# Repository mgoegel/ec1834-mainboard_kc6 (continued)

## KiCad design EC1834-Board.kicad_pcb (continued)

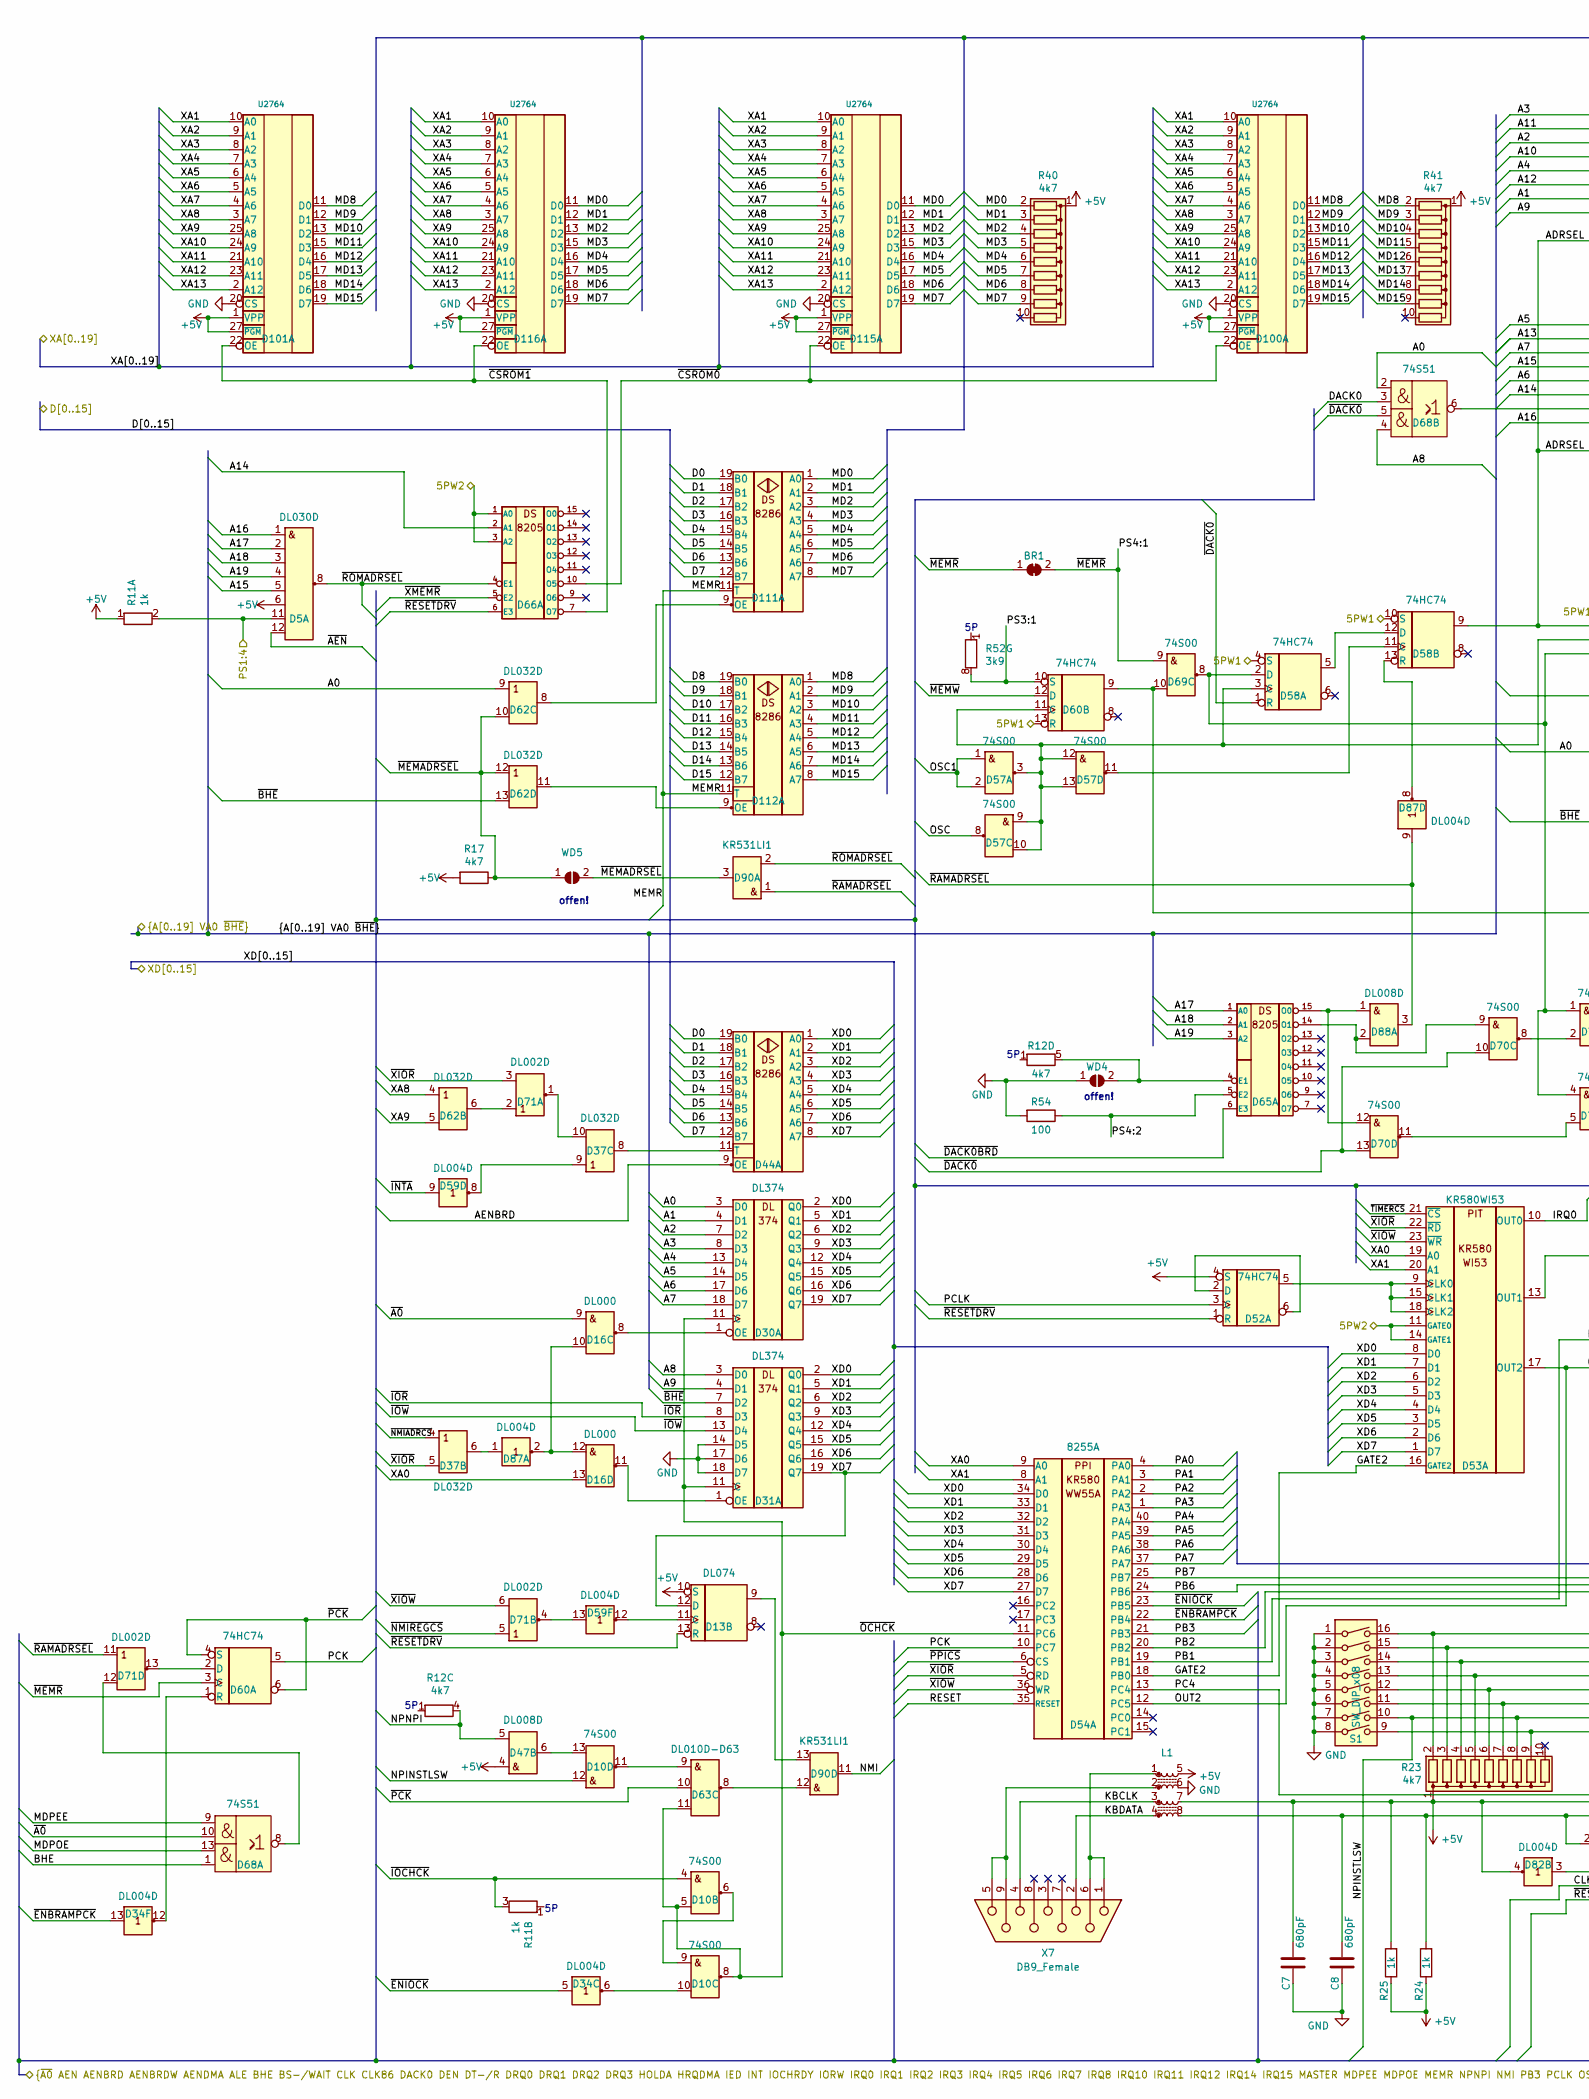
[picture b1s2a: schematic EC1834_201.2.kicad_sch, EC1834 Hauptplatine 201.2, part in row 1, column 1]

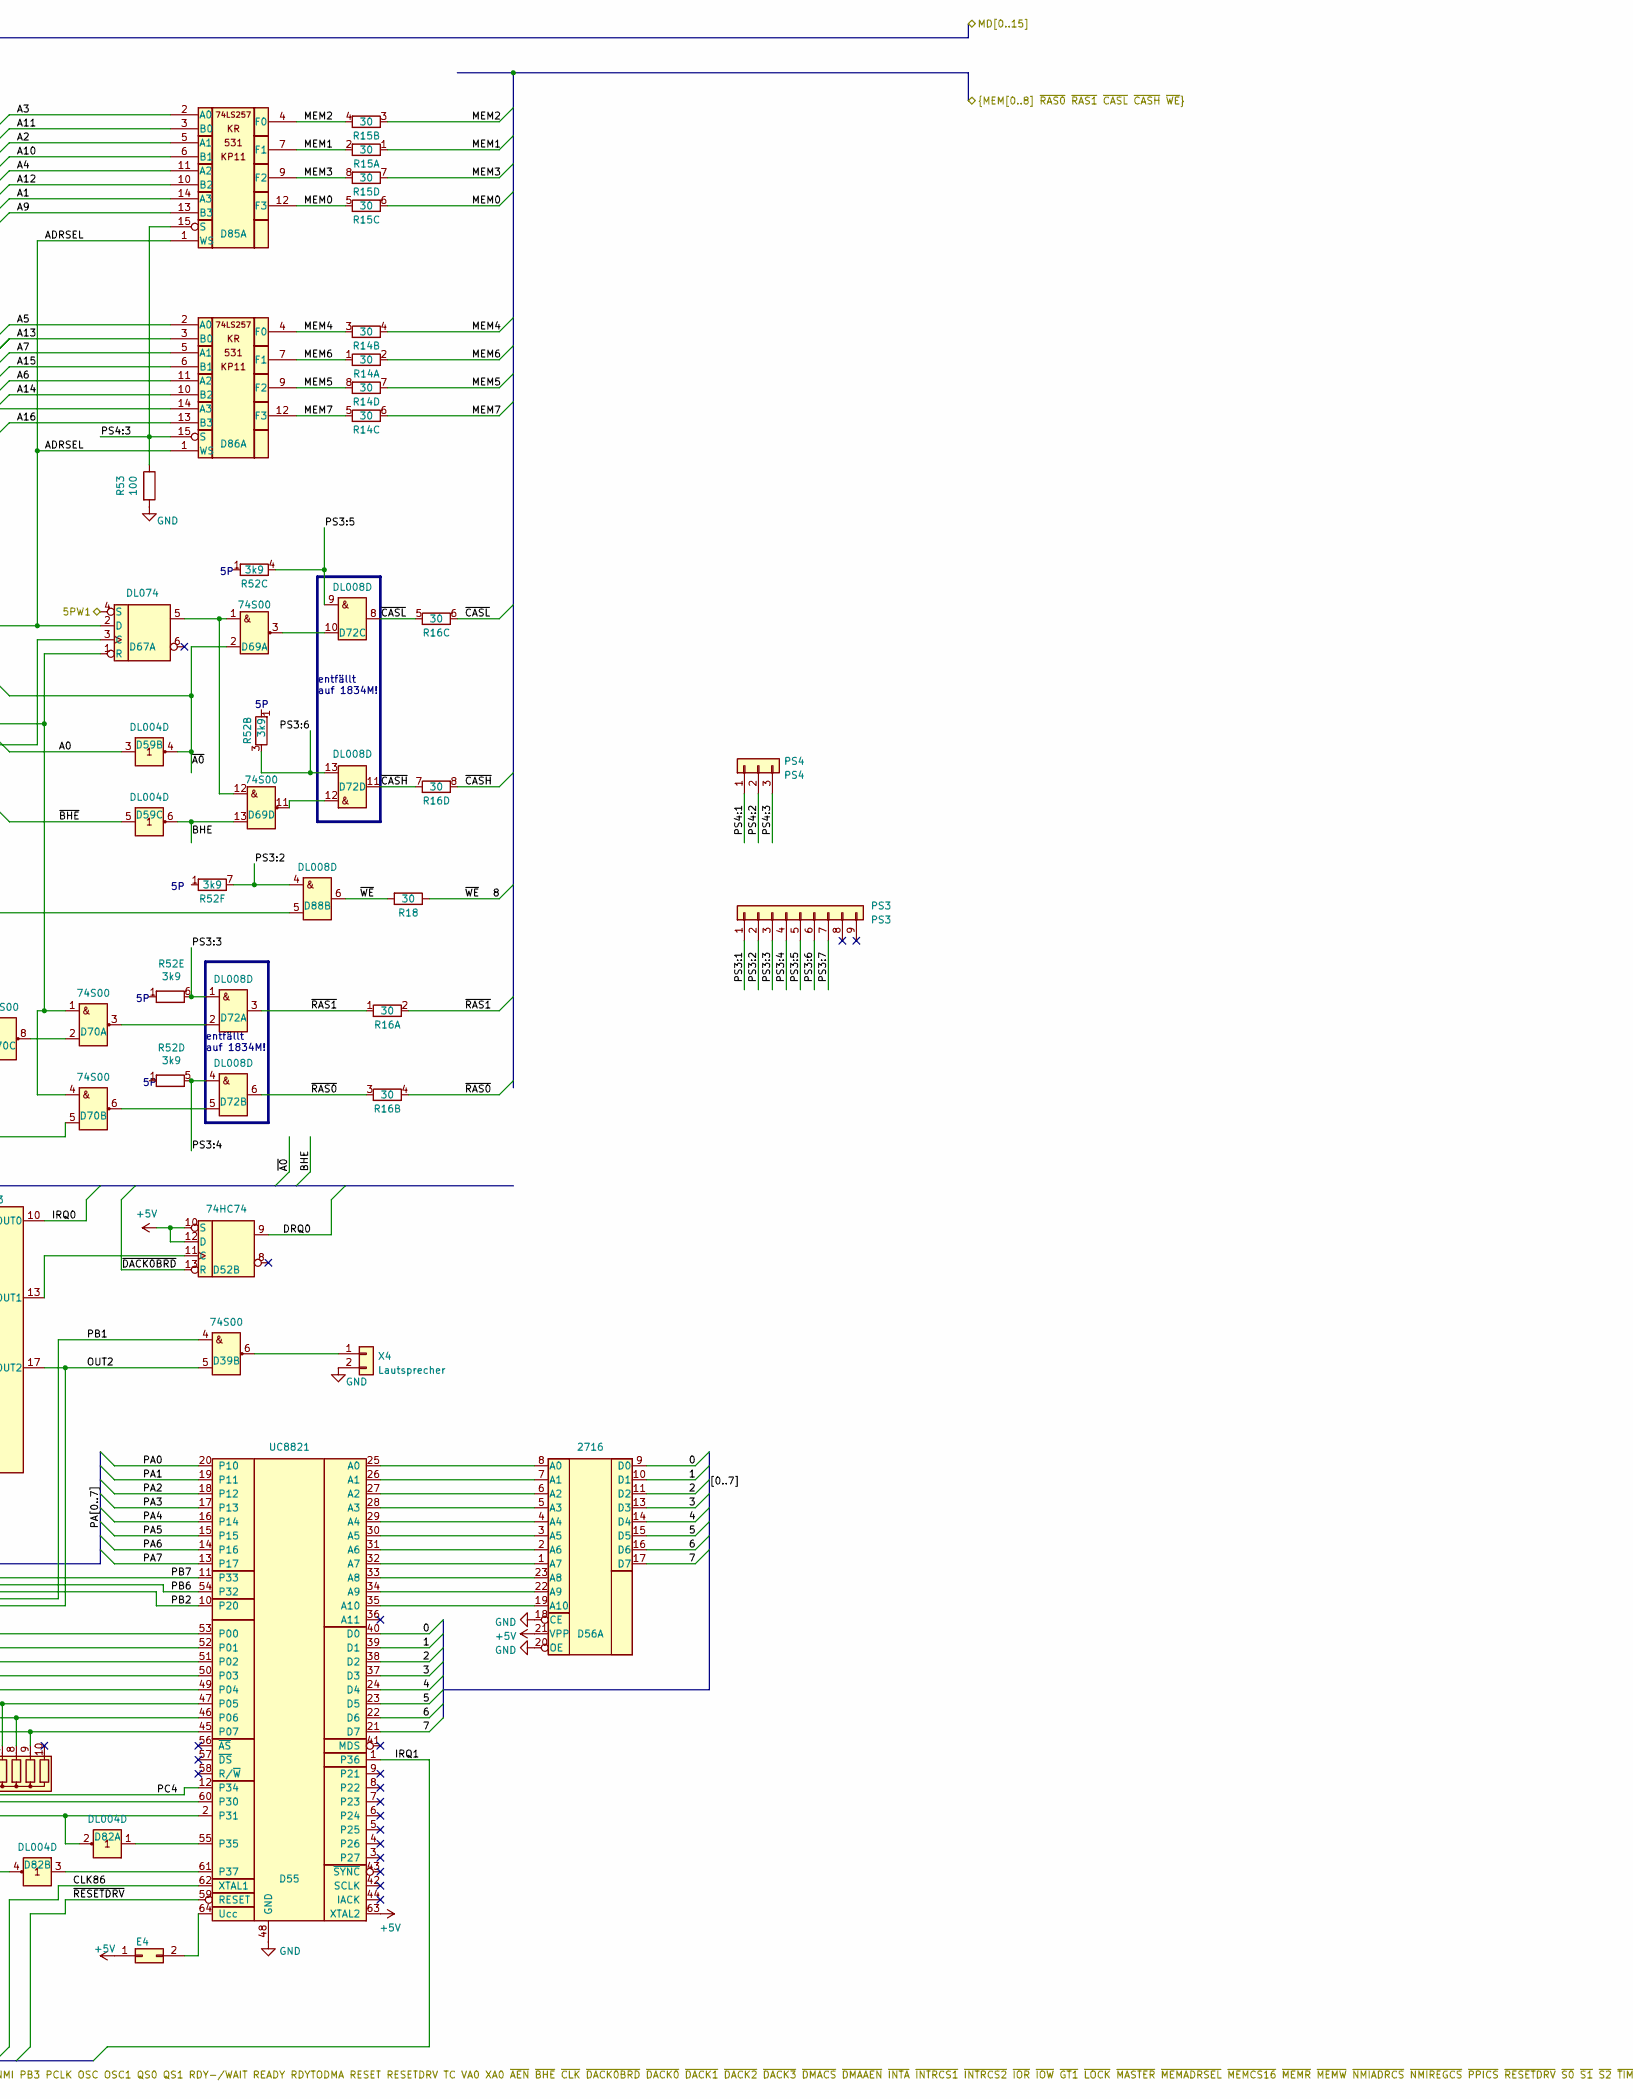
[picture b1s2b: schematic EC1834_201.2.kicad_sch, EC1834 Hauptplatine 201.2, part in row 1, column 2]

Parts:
BR1: SolderJumper_2_Bridged; R_Axial_DIN0204_L3.6mm_D1.6mm_P7.62mm_Horizontal
C7, C8: 680pF; C_Disc_D4.3mm_W1.9mm_P5.00mm
D5: DL030D; DIP-14_W7.62mm
D10, D39, D57, D69, D70: 74S00; DIP-14_W7.62mm
D13, D67: DL074; DIP-14_W7.62mm
D16: DL000; DIP-14_W7.62mm
D30, D31: DL374; DIP-20_W7.62mm
D34, D59, D82, D87: DL004D; DIP-14_W7.62mm
D37, D62: DL032D; DIP-14_W7.62mm
D44, D111, D112: DS8286D-D111; DIP-20_W7.62mm
D47, D72, D88: DL008D; DIP-14_W7.62mm
D52, D58, D60: 74HC74; DIP-14_W7.62mm
D53: KR580WI53; DIP-24_W15.24mm
D54: 8255A; DIP-40_W15.24mm
D55: UC8821; EMR-64_W22.86mm
D56: 2716; DIP-24_W15.24mm
D63: DL010D-D63; DIP-14_W7.62mm
D65, D66: DS8205; DIP-16_W7.62mm
D68: 74S51; DIP-14_W7.62mm
D71: DL002D; DIP-14_W7.62mm
D85, D86: KR531KP11; DIP-16_W7.62mm
D90: KR531LI1; DIP-14_W7.62mm
D100, D101, D115, D116: U2764; DIP-28_W15.24mm
E4: SolderJumper_2_Bridged; PinHeader_1x02_P2.54mm_Vertical
L1: L_Ferrite_Coupled_Small_15263748; DIP-8_W7.62mm
PS3: PS3; PinHeader_1x09_P2.54mm_Vertical
PS4: PS4; PinHeader_1x03_P2.54mm_Vertical
R11: 1k; R_Array_SIP6
R12, R23, R40, R41: 4k7; R_Array_SIP10
R14, R15, R16: 30; R_Array_SIP8
R17: 4k7; R_Axial_L9.0mm_D1.8mm_P12.70mm_Horizontal
R18: 30; R_Axial_L9.0mm_D1.8mm_P12.70mm_Horizontal
R24, R25: 1k; R_Axial_L9.0mm_D1.8mm_P12.70mm_Horizontal
R52: 3k9; R_Array_SIP8
R53, R54: 100; R_Axial_L9.0mm_D1.8mm_P12.70mm_Horizontal
S1: SW_DIP_x08; SW_DIP_SPSTx08_Slide_9.78x22.5mm_W7.62mm_P2.54mm
WD4: SolderJumper_2_Open; R_Axial_DIN0204_L3.6mm_D1.6mm_P7.62mm_Horizontal
WD5: SolderJumper_2_Bridged; R_Axial_DIN0204_L3.6mm_D1.6mm_P7.62mm_Horizontal
X4: Lautsprecher; PinHeader_1x02_P2.54mm_Vertical
X7: DB9_Female; DSUB-9_Female_Horizontal_P2.77x2.84mm_EdgePinOffset9.90mm_H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

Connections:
5PW1: D58.4 (S), D58.10 (S), D60.13 (R), D67.4 (S); also elsewhere on the board
5PW2: D53.11 (GATE0), D53.14 (GATE1), D66.1 (A0), D66.3 (A2); also elsewhere on the board
+5V: C7.1, D5.6 (F), D13.10 (S), D47.4 (A2), D52.4 (S), D52.10 (S), D52.12 (D), D55.60 (P30), D55.63 (XTAL2), D56.21 (VPP), D82.4 (Y2), D100.1 (VPP), D100.27 (~PGM), D101.1 (VPP), D101.27 (~PGM), D115.1 (VPP), D115.27 (~PGM), D116.1 (VPP), D116.27 (~PGM), E4.1, L1.5, L1.7, R11.1 (R1.1), R17.2, R23.1 (common), R24.1, R25.1, R25.2, R40.1 (common), R41.1 (common); also elsewhere on the board
/EC1834 201.1/A0: D30.3 (D0), D59.3 (A2), D62.9 (A3), D68.2; also elsewhere on the board
/EC1834 201.1/A1: D30.4 (D1), D85.14 (A3); also elsewhere on the board
/EC1834 201.1/A2: D30.7 (D2), D85.5 (A1); also elsewhere on the board
/EC1834 201.1/A3: D30.8 (D3), D85.2 (A0); also elsewhere on the board
/EC1834 201.1/A4: D30.13 (D4), D85.11 (A2); also elsewhere on the board
/EC1834 201.1/A5: D30.14 (D5), D86.2 (A0); also elsewhere on the board
/EC1834 201.1/A6: D30.17 (D6), D86.11 (A2); also elsewhere on the board
/EC1834 201.1/A7: D30.18 (D7), D86.5 (A1); also elsewhere on the board
/EC1834 201.1/A8: D31.3 (D0), D68.4; also elsewhere on the board
/EC1834 201.1/A9: D31.4 (D1), D85.13 (B3); also elsewhere on the board
/EC1834 201.1/A10: D85.6 (B1); also elsewhere on the board
/EC1834 201.1/A11: D85.3 (B0); also elsewhere on the board
/EC1834 201.1/A12: D85.10 (B2); also elsewhere on the board
/EC1834 201.1/A13: D86.3 (B0); also elsewhere on the board
/EC1834 201.1/A14: D66.2 (A1), D86.10 (B2); also elsewhere on the board
/EC1834 201.1/A15: D5.5 (E), D86.6 (B1); also elsewhere on the board
/EC1834 201.1/A16: D5.1 (A), D86.13 (B3); also elsewhere on the board
/EC1834 201.1/A17: D5.2 (B), D65.1 (A0); also elsewhere on the board
/EC1834 201.1/A18: D5.3 (C), D65.2 (A1); also elsewhere on the board
/EC1834 201.1/A19: D5.4 (D), D65.3 (A2); also elsewhere on the board
/EC1834 201.1/AENBRD: D44.9 (OE); also elsewhere on the board
/EC1834 201.1/BHE: D59.6 (Y3), D68.1, D69.13 (B4); also elsewhere on the board
/EC1834 201.1/CLK86: D55.62 (XTAL1); also elsewhere on the board
/EC1834 201.1/D0: D44.19 (B0), D111.19 (B0); also elsewhere on the board
/EC1834 201.1/D1: D44.18 (B1), D111.18 (B1); also elsewhere on the board
/EC1834 201.1/D2: D44.17 (B2), D111.17 (B2); also elsewhere on the board
/EC1834 201.1/D3: D44.16 (B3), D111.16 (B3); also elsewhere on the board
/EC1834 201.1/D4: D44.15 (B4), D111.15 (B4); also elsewhere on the board
/EC1834 201.1/D5: D44.14 (B5), D111.14 (B5); also elsewhere on the board
/EC1834 201.1/D6: D44.13 (B6), D111.13 (B6); also elsewhere on the board
/EC1834 201.1/D7: D44.12 (B7), D111.12 (B7); also elsewhere on the board
/EC1834 201.1/D8: D112.19 (B0); also elsewhere on the board
/EC1834 201.1/D9: D112.18 (B1); also elsewhere on the board
/EC1834 201.1/D10: D112.17 (B2); also elsewhere on the board
/EC1834 201.1/D11: D112.16 (B3); also elsewhere on the board
/EC1834 201.1/D12: D112.15 (B4); also elsewhere on the board
/EC1834 201.1/D13: D112.14 (B5); also elsewhere on the board
/EC1834 201.1/D14: D112.13 (B6); also elsewhere on the board
/EC1834 201.1/D15: D112.12 (B7); also elsewhere on the board
/EC1834 201.1/DACK0: D68.3; also elsewhere on the board
/EC1834 201.1/DRQ0: D52.9; also elsewhere on the board
/EC1834 201.1/IRQ0: D53.10 (OUT0); also elsewhere on the board
/EC1834 201.1/IRQ1: D55.1 (P36); also elsewhere on the board
/EC1834 201.1/MDPEE: D68.9; also elsewhere on the board
/EC1834 201.1/MDPOE: D68.13; also elsewhere on the board
/EC1834 201.1/MEMR: D111.11 (T), D112.11 (T); also elsewhere on the board
/EC1834 201.1/NMI: D90.11 (Y4); also elsewhere on the board
/EC1834 201.1/NPNPI: D47.5 (B2), R12.4 (R3.2); also elsewhere on the board
/EC1834 201.1/OSC: D57.8 (Y3); also elsewhere on the board
/EC1834 201.1/OSC1: D57.1 (A1), D57.2 (B1); also elsewhere on the board
/EC1834 201.1/PB3: D54.21 (PB3); also elsewhere on the board
/EC1834 201.1/PCLK: D52.3 (C); also elsewhere on the board
/EC1834 201.1/PS1:4: D5.11 (G), R11.2 (R1.2); also elsewhere on the board
/EC1834 201.1/RESET: D54.35 (RESET); also elsewhere on the board
/EC1834 201.1/XA0: D16.13 (B4), D53.19 (A0), D54.9 (A0); also elsewhere on the board
/EC1834 201.1/XA1: D53.20 (A1), D54.8 (A1), D100.10 (A0), D101.10 (A0), D115.10 (A0), D116.10 (A0); also elsewhere on the board
/EC1834 201.1/XA2: D100.9 (A1), D101.9 (A1), D115.9 (A1), D116.9 (A1); also elsewhere on the board
/EC1834 201.1/XA3: D100.8 (A2), D101.8 (A2), D115.8 (A2), D116.8 (A2); also elsewhere on the board
/EC1834 201.1/XA4: D100.7 (A3), D101.7 (A3), D115.7 (A3), D116.7 (A3); also elsewhere on the board
/EC1834 201.1/XA5: D100.6 (A4), D101.6 (A4), D115.6 (A4), D116.6 (A4); also elsewhere on the board
/EC1834 201.1/XA6: D100.5 (A5), D101.5 (A5), D115.5 (A5), D116.5 (A5); also elsewhere on the board
/EC1834 201.1/XA7: D100.4 (A6), D101.4 (A6), D115.4 (A6), D116.4 (A6); also elsewhere on the board
/EC1834 201.1/XA8: D62.4 (A2), D100.3 (A7), D101.3 (A7), D115.3 (A7), D116.3 (A7); also elsewhere on the board
/EC1834 201.1/XA9: D62.5 (B2), D100.25 (A8), D101.25 (A8), D115.25 (A8), D116.25 (A8); also elsewhere on the board
/EC1834 201.1/XA10: D100.24 (A9), D101.24 (A9), D115.24 (A9), D116.24 (A9); also elsewhere on the board
/EC1834 201.1/XA11: D100.21 (A10), D101.21 (A10), D115.21 (A10), D116.21 (A10); also elsewhere on the board
/EC1834 201.1/XA12: D100.23 (A11), D101.23 (A11), D115.23 (A11), D116.23 (A11); also elsewhere on the board
/EC1834 201.1/XA13: D100.2 (A12), D101.2 (A12), D115.2 (A12), D116.2 (A12); also elsewhere on the board
/EC1834 201.1/XD0: D30.2 (Q0), D31.2 (Q0), D44.1 (A0), D53.8 (D0), D54.34 (D0); also elsewhere on the board
/EC1834 201.1/XD1: D30.5 (Q1), D31.5 (Q1), D44.2 (A1), D53.7 (D1), D54.33 (D1); also elsewhere on the board
/EC1834 201.1/XD2: D30.6 (Q2), D31.6 (Q2), D44.3 (A2), D53.6 (D2), D54.32 (D2); also elsewhere on the board
/EC1834 201.1/XD3: D30.9 (Q3), D31.9 (Q3), D44.4 (A3), D53.5 (D3), D54.31 (D3); also elsewhere on the board
/EC1834 201.1/XD4: D30.12 (Q4), D31.12 (Q4), D44.5 (A4), D53.4 (D4), D54.30 (D4); also elsewhere on the board
/EC1834 201.1/XD5: D30.15 (Q5), D31.15 (Q5), D44.6 (A5), D53.3 (D5), D54.29 (D5); also elsewhere on the board
/EC1834 201.1/XD6: D30.16 (Q6), D31.16 (Q6), D44.7 (A6), D53.2 (D6), D54.28 (D6); also elsewhere on the board
/EC1834 201.1/XD7: D13.12 (D), D30.19 (Q7), D31.19 (Q7), D44.8 (A7), D53.1 (D7), D54.27 (D7); also elsewhere on the board
/EC1834 201.1/~A0: D16.9 (A3), D59.4 (Y2), D68.10, D69.2 (B1); also elsewhere on the board
/EC1834 201.1/~AEN: D5.12 (H); also elsewhere on the board
/EC1834 201.1/~BHE: D31.7 (D2), D59.5 (A3), D62.13 (B4); also elsewhere on the board
/EC1834 201.1/~DACK0BRD: D52.13 (R), D65.6 (E3); also elsewhere on the board
/EC1834 201.1/~DACK0: D58.1 (R), D68.5, D70.10 (B3), D70.13 (B4); also elsewhere on the board
/EC1834 201.1/~INTA: D59.9 (A4); also elsewhere on the board
/EC1834 201.1/~IOR: D31.8 (D3); also elsewhere on the board
/EC1834 201.1/~IOW: D31.13 (D4); also elsewhere on the board
/EC1834 201.1/~MEMADRSEL: D62.10 (B3), D62.12 (A4), D90.3 (Y1), R17.1, WD5.1 (A), WD5.2 (B); also elsewhere on the board
/EC1834 201.1/~MEMR: BR1.1 (A), BR1.2 (B), D60.3 (C), D69.9 (A3), PS4.1; also elsewhere on the board
/EC1834 201.1/~MEMW: D60.12 (D); also elsewhere on the board
/EC1834 201.1/~NMIADRCS: D37.4 (A2); also elsewhere on the board
/EC1834 201.1/~NMIREGCS: D71.5 (A2); also elsewhere on the board
/EC1834 201.1/~PPICS: D54.6 (CS); also elsewhere on the board
/EC1834 201.1/~RESETDRV: D13.13 (R), D52.1 (R), D55.59 (RESET), D66.6 (E3); also elsewhere on the board
/EC1834 201.1/~TIMERCS: D53.21 (~CS); also elsewhere on the board
/EC1834 201.1/~XIOR: D37.5 (B2), D53.22 (~RD), D54.5 (RD), D71.3 (B1); also elsewhere on the board
/EC1834 201.1/~XIOW: D53.23 (~WR), D54.36 (WR), D71.6 (B2); also elsewhere on the board
/EC1834 201.1/~XMEMR: D66.5 (E2); also elsewhere on the board
/EC1834 201.2/0: D55.40 (D0), D56.9 (D0)
/EC1834 201.2/1: D55.39 (D1), D56.10 (D1)
/EC1834 201.2/2: D55.38 (D2), D56.11 (D2)
/EC1834 201.2/3: D55.37 (D3), D56.13 (D3)
/EC1834 201.2/4: D55.24 (D4), D56.14 (D4)
/EC1834 201.2/5: D55.23 (D5), D56.15 (D5)
/EC1834 201.2/6: D55.22 (D6), D56.16 (D6)
/EC1834 201.2/7: D55.21 (D7), D56.17 (D7)
/EC1834 201.2/ADRSEL: D58.9, D67.2 (D), D85.1 (WS), D86.1 (WS)
/EC1834 201.2/GATE2: D53.16 (GATE2), D54.18 (PB0)
/EC1834 201.2/KBCLK: L1.3, X7.4
/EC1834 201.2/KBDATA: L1.4, X7.2
/EC1834 201.2/MEM0: D85.12 (F3), R15.5 (R3.1), R15.6 (R3.2)
/EC1834 201.2/MEM1: D85.7 (F1), R15.1 (R1.1), R15.2 (R1.2)
/EC1834 201.2/MEM2: D85.4 (F0), R15.3 (R2.1), R15.4 (R2.2)
/EC1834 201.2/MEM3: D85.9 (F2), R15.7 (R4.1), R15.8 (R4.2)
/EC1834 201.2/MEM4: D86.4 (F0), R14.3 (R2.1), R14.4 (R2.2)
/EC1834 201.2/MEM5: D86.9 (F2), R14.7 (R4.1), R14.8 (R4.2)
/EC1834 201.2/MEM6: D86.7 (F1), R14.1 (R1.1), R14.2 (R1.2)
/EC1834 201.2/MEM7: D86.12 (F3), R14.5 (R3.1), R14.6 (R3.2)
/EC1834 201.2/NPINSTLSW: D10.12 (A4), D55.46 (P06), R23.8 (R7), S1.10
/EC1834 201.2/OUT2: D39.5 (B2), D53.17 (OUT2), D54.12 (PC5)
/EC1834 201.2/PA0: D54.4 (PA0), D55.20 (P10)
/EC1834 201.2/PA1: D54.3 (PA1), D55.19 (P11)
/EC1834 201.2/PA2: D54.2 (PA2), D55.18 (P12)
/EC1834 201.2/PA3: D54.1 (PA3), D55.17 (P13)
/EC1834 201.2/PA4: D54.40 (PA4), D55.16 (P14)
/EC1834 201.2/PA5: D54.39 (PA5), D55.15
/EC1834 201.2/PA6: D54.38 (PA6), D55.14 (P16)
/EC1834 201.2/PA7: D54.37 (PA7), D55.13 (P17)
/EC1834 201.2/PB1: D39.4 (A2), D54.19 (PB1)
/EC1834 201.2/PB2: D54.20 (PB2), D55.10 (P20)
/EC1834 201.2/PB6: D54.24 (PB6), D55.54 (P32)
/EC1834 201.2/PB7: D54.25 (PB7), D55.11 (P33)
/EC1834 201.2/PC4: D54.13 (PC4), D55.12 (P34)
/EC1834 201.2/PCK: D54.10 (PC7), D60.5
/EC1834 201.2/PS3:1: D60.10 (S), PS3.1, R52.8 (R7.2)
/EC1834 201.2/PS3:2: D88.4 (A2), PS3.2, R52.7 (R6.2)
/EC1834 201.2/PS3:3: D72.1 (A1), PS3.3, R52.6 (R5.2)
/EC1834 201.2/PS3:4: D72.4 (A2), PS3.4, R52.5 (R4.2)
/EC1834 201.2/PS3:5: D72.9 (A3), PS3.5, R52.4 (R3.2)
/EC1834 201.2/PS3:6: D72.13 (B4), PS3.6, R52.3 (R2.2)
/EC1834 201.2/PS3:7: PS3.7
/EC1834 201.2/PS4:2: D65.5 (E2), PS4.2, R54.1
/EC1834 201.2/PS4:3: D85.15 (S), D86.15 (S), PS4.3, R53.1
/EC1834 201.2/~CSROM0: D66.10 (O5), D100.22 (OE), D115.22 (OE)
/EC1834 201.2/~CSROM1: D66.7 (O7), D101.22 (OE), D116.22 (OE)
/EC1834 201.2/~ENBRAMPCK: D34.13 (A6), D54.22 (PB4)
/EC1834 201.2/~ENIOCK: D34.5 (A3), D54.23 (PB5)
/EC1834 201.2/~IOCHCK: D10.4 (A2), R11.3 (R2.2)
/EC1834 201.2/~OCHCK: D10.5 (B2), D10.8 (Y3), D30.11 (C), D31.11 (C), D54.11 (PC6), D63.11 (C3)
/EC1834 201.2/~PCK: D60.4 (S), D60.6, D63.10 (B3)
/EC1834 201.2/~RAMADRSEL: D71.11 (A4), D87.9 (A4), D88.3 (Y1), D90.1 (A1)
/EC1834 201.2/~ROMADRSEL: D5.8 (Y), D66.4 (E1), D90.2 (B1)
/EC1834_201.3 RAM/MD0: D111.1 (A0), D115.11 (D0), D116.11 (D0), R40.2 (R1); also elsewhere on the board
/EC1834_201.3 RAM/MD1: D111.2 (A1), D115.12 (D1), D116.12 (D1), R40.3 (R2); also elsewhere on the board
/EC1834_201.3 RAM/MD2: D111.3 (A2), D115.13 (D2), D116.13 (D2), R40.4 (R3); also elsewhere on the board
/EC1834_201.3 RAM/MD3: D111.4 (A3), D115.15 (D3), D116.15 (D3), R40.5 (R4); also elsewhere on the board
/EC1834_201.3 RAM/MD4: D111.5 (A4), D115.16 (D4), D116.16 (D4), R40.6 (R5); also elsewhere on the board
/EC1834_201.3 RAM/MD5: D111.6 (A5), D115.17 (D5), D116.17 (D5), R40.7 (R6); also elsewhere on the board
/EC1834_201.3 RAM/MD6: D111.7 (A6), D115.18 (D6), D116.18 (D6), R40.8 (R7); also elsewhere on the board
/EC1834_201.3 RAM/MD7: D111.8 (A7), D115.19 (D7), D116.19 (D7), R40.9 (R8); also elsewhere on the board
/EC1834_201.3 RAM/MD8: D100.11 (D0), D101.11 (D0), D112.1 (A0), R41.2 (R1); also elsewhere on the board
/EC1834_201.3 RAM/MD9: D100.12 (D1), D101.12 (D1), D112.2 (A1), R41.3 (R2); also elsewhere on the board
/EC1834_201.3 RAM/MD10: D100.13 (D2), D101.13 (D2), D112.3 (A2), R41.4 (R3); also elsewhere on the board
/EC1834_201.3 RAM/MD11: D100.15 (D3), D101.15 (D3), D112.4 (A3), R41.5 (R4); also elsewhere on the board
/EC1834_201.3 RAM/MD12: D100.16 (D4), D101.16 (D4), D112.5 (A4), R41.6 (R5); also elsewhere on the board
/EC1834_201.3 RAM/MD13: D100.17 (D5), D101.17 (D5), D112.6 (A5), R41.7 (R6); also elsewhere on the board
/EC1834_201.3 RAM/MD14: D100.18 (D6), D101.18 (D6), D112.7 (A6), R41.8 (R7); also elsewhere on the board
/EC1834_201.3 RAM/MD15: D100.19 (D7), D101.19 (D7), D112.8 (A7), R41.9 (R8); also elsewhere on the board
/EC1834_201.3 RAM/~CASH: D72.11 (Y4), R16.7 (R4.1), R16.8 (R4.2); also elsewhere on the board
/EC1834_201.3 RAM/~CASL: D72.8 (Y3), R16.5 (R3.1), R16.6 (R3.2); also elsewhere on the board
/EC1834_201.3 RAM/~RAS0: D72.6 (Y2), R16.3 (R2.1), R16.4 (R2.2); also elsewhere on the board
/EC1834_201.3 RAM/~RAS1: D72.3 (Y1), R16.1 (R1.1), R16.2 (R1.2); also elsewhere on the board
/EC1834_201.3 RAM/~WE: D88.6 (Y2), R18.1, R18.2; also elsewhere on the board
GND: C7.2, C8.2, D31.14 (D5), D31.17 (D6), D31.18 (D7), D55.48 (GND), D56.18 (CE), D56.20 (OE), D100.20 (CS), D101.20 (CS), D115.20 (CS), D116.20 (CS), L1.6, R53.2, R54.2, S1.1, S1.2, S1.3, S1.4, S1.5, S1.6, S1.7, S1.8, WD4.1 (A), X4.2; also elsewhere on the board
unnamed: C8.1, D55.2 (P31), D82.2 (Y1), L1.8, R24.2
unnamed: D10.6 (Y2), D10.9 (A3)
unnamed: D10.10 (B3), D34.6 (Y3)
unnamed: D10.11 (Y4), D63.9 (A3)
unnamed: D10.13 (B4), D47.6 (Y2)
unnamed: D13.9, D90.13 (B4)
unnamed: D13.11 (C), D59.12 (Y6)
unnamed: D16.8 (Y3), D30.1 (OE)
unnamed: D16.10 (B3), D16.12 (A4), D87.2 (Y1)
unnamed: D16.11 (Y4), D31.1 (OE)
unnamed: D34.12 (Y6), D60.1 (R)
unnamed: D37.6 (Y2), D87.1 (A1)
unnamed: D37.8 (Y3), D44.11 (T)
unnamed: D37.9 (A3), D59.8 (Y4)
unnamed: D37.10 (B3), D71.1 (Y1)
unnamed: D39.6 (Y2), X4.1
unnamed: D52.2 (D), D52.6
unnamed: D52.5, D53.9 (CLK0), D53.15 (CLK1), D53.18 (CLK2)
unnamed: D52.11 (C), D53.13 (OUT1)
unnamed: D55.25 (A0), D56.8 (A0)
unnamed: D55.26 (A1), D56.7 (A1)
unnamed: D55.27 (A2), D56.6 (A2)
unnamed: D55.28 (A3), D56.5 (A3)
unnamed: D55.29 (A4), D56.4 (A4)
unnamed: D55.30 (A5), D56.3 (A5)
unnamed: D55.31 (A6), D56.2 (A6)
unnamed: D55.32 (A7), D56.1 (A7)
unnamed: D55.33 (A8), D56.23 (A8)
unnamed: D55.34 (A9), D56.22 (A9)
unnamed: D55.35 (A10), D56.19 (A10)
unnamed: D55.45 (P07), R23.9 (R8), S1.9
unnamed: D55.47 (P05), R23.7 (R6), S1.11
unnamed: D55.49 (P04), R23.6 (R5), S1.12
unnamed: D55.50 (P03), R23.5 (R4), S1.13
unnamed: D55.51 (P02), R23.4 (R3), S1.14
unnamed: D55.52 (P01), R23.3 (R2), S1.15
unnamed: D55.53 (P00), R23.2 (R1), S1.16
unnamed: D55.55 (P35), D82.1 (A1)
unnamed: D55.61 (P37), D82.3 (A2)
unnamed: D55.64 (Ucc), E4.2
unnamed: D57.3 (Y1), D57.9 (A3), D57.10 (B3), D57.12 (A4), D57.13 (B4), D58.3 (C), D60.11 (C), D67.3 (C)
unnamed: D57.11 (Y4), D58.11 (C)
unnamed: D58.2 (D), D67.1 (R), D69.8 (Y3), D70.1 (A1), D70.4 (A2)
unnamed: D58.5, D58.12 (D)
unnamed: D58.13 (R), D87.8 (Y4)
unnamed: D59.13 (A6), D71.4 (Y2)
unnamed: D60.2 (D), D71.13 (Y4)
unnamed: D60.9, D69.10 (B3), D88.5 (B2)
unnamed: D62.6 (Y2), D71.2 (A1)
unnamed: D63.8 (Y3), D90.12 (A4)
unnamed: D65.4 (E1), R12.5 (R4.2), WD4.2 (B)
unnamed: D65.14 (O1), D70.9 (A3), D88.2 (B1)
unnamed: D65.15 (O0), D70.12 (A4), D88.1 (A1)
unnamed: D67.5, D69.1 (A1), D69.12 (A4)
unnamed: D68.6, D86.14 (A3)
unnamed: D68.8, D71.12 (B4)
unnamed: D69.3 (Y1), D72.10 (B3)
unnamed: D69.11 (Y4), D72.12 (A4)
unnamed: D70.2 (B1), D70.8 (Y3)
unnamed: D70.3 (Y1), D72.2 (B1)
unnamed: D70.6 (Y2), D72.5 (B2)
unnamed: D70.5 (B2), D70.11 (Y4)
unnamed: D62.8 (Y3), D111.9 (OE)
unnamed: D62.11 (Y4), D112.9 (OE)
unnamed: L1.1, X7.1, X7.6
unnamed: L1.2, X7.5, X7.9

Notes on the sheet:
offen!
entfällt auf 1834M!
